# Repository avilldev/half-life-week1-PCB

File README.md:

# Astrobie: A close encounter in your pocket

## What it is

Astrobie is a custom-designed PCB digital pet powered by a Seeed XIAO ESP32-C3. This project was made for the first-week PCB submission for Hackclub's [Half Life](https://halflife.hackclub.com/?ref=1941)
program. It is based on their beginner guide, [Starbie](https://github.com/SharKingStudios/Starbie/blob/main/Week%201%20Guide.md). However, I customized the project to have a different theme.
It features a UFO-themed circuit board, a 128x64 OLED screen displaying an alien sprite, an MPU6050 accelerometer, a DHT11 temperature/humidity sensor, and two push buttons.

## How it works

The pet wanders around the OLED screen.

- **Motion Control:** After pressing the menu button, the board can be tilted to select actions such as Fuel, Fly, Scan, or Dock.
- **Animations:** Each action has an animation. For example, selecting the Dock action triggers a nap cycle with floating "z" characters.
- **Sensors:** The MPU6050 detects shaking to wake the pet up. The DHT11 reads real-world room temperature and humidity to display in the stats.

## Social

Here are the short videos that I have posted related to my project (YouTube Shorts):

- **Idea:** https://www.youtube.com/shorts/dOhUSb0GdCU
- **5 Hours Progress:** https://www.youtube.com/shorts/tnYaCUamZv8

[#hackclubhalflife](https://www.youtube.com/hashtag/hackclubhalflife)
[#hackclub](https://www.youtube.com/hashtag/hackclub)

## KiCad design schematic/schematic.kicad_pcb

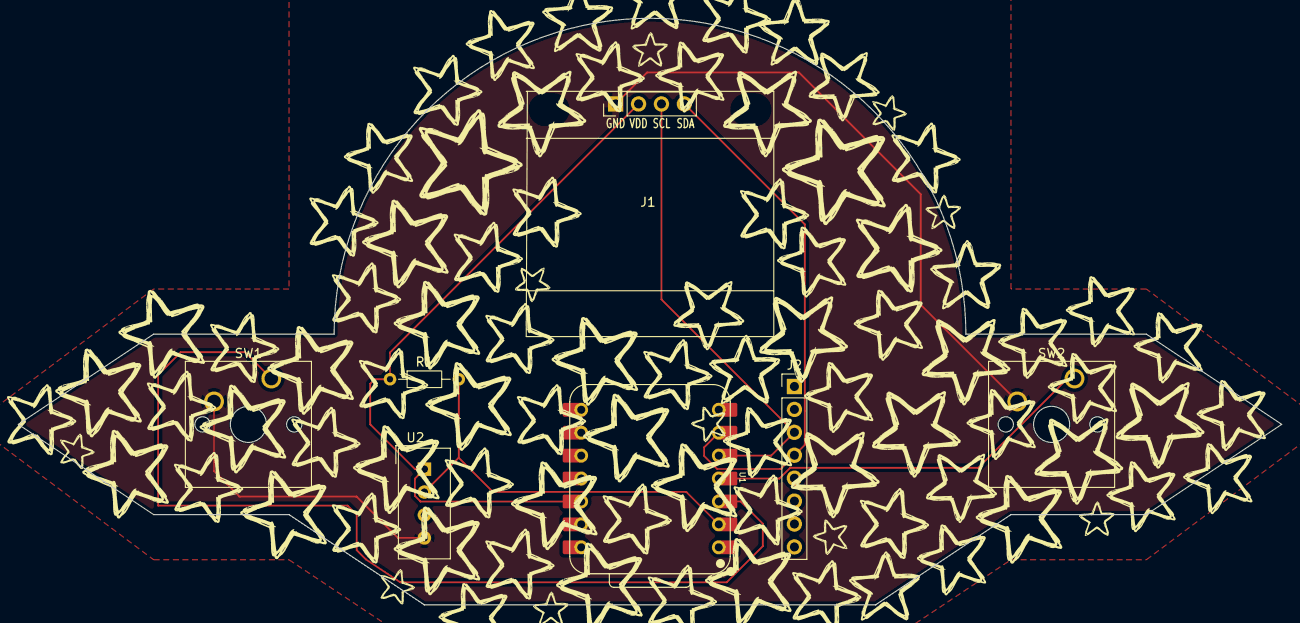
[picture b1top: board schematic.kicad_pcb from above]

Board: 2 copper layers, 140.0 x 65.0 mm, 7 parts (0 on the bottom side), 7 nets.

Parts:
J1: Conn_01x04_Pin; Display_128x64_096_I2C
J2: Conn_01x08_Pin; PinHeader_1x08_P2.54mm_Vertical
R1: 10k; R_Axial_DIN0204_L3.6mm_D1.6mm_P7.62mm_Horizontal
SW1, SW2: SW_Push; SW_Cherry_MX_1.00u_PCB
U1: XIAO-ESP32-C3-SMD; XIAO-ESP32-C6-DIP
U2: DHT11; Aosong_DHT11_5.5x12.0_P2.54mm

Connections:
+3.3V: J1.2, R1.1, U1.12 (3V3_OUT), U2.1 (VDD)
/DHT11 DATA: R1.2, U1.2 (D1), U2.2 (DATA)
/GPIO2: SW1.1, U1.3 (D2)
/GPIO3: SW2.1, U1.4 (D3)
/SCL: J1.3, J2.3, U1.5 (D4)
/SDA: J1.4, J2.4, U1.6 (D5)
GND: J1.1, SW1.2, SW2.2, U1.13 (GND), U2.4 (GND)
